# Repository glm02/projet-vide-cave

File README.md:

# Projet vide-cave — GEII

> **En bref** — Projet de BUT GEII : une carte électronique qui surveille et commande
> la pompe d'un vide-cave — **mesure du courant** du moteur, autotest périodique,
> affichage sur écran LCD, alertes par LED et buzzer. Conçue sous **KiCad**,
> programmée en **C sur PIC** (MPLAB X, MCC), étudiée sous **LTspice**, mise en scène
> dans **Blender**, suivie dans **Obsidian**.

| Bloc | Rôle |
|---|---|
| PIC16F1788 | Acquisition, décision, affichage et commande |
| Capteur de courant (ACS756) | Mesure du courant du moteur de la pompe |
| Optotriac + triac de puissance | Commande de la pompe sur le secteur, isolée de l'électronique basse tension |
| LCD 162B, LED, buzzer | Affichage de l'état et alertes |

Statut : conception en cours — voir plus bas ce qui reste à câbler et à valider.

**Ce que j'ai fait :** reprise et nettoyage de la carte KiCad, comparaison schéma/PCB/
nomenclature, dimensionnement de l'optotriac (MOC3041) avec bancs LTspice, maquette
3D de l'installation, visualisation interactive de la carte, et organisation du projet
pour travailler à deux sous Git.

---

Étude d'une commande de pompe vide-cave avec surveillance du courant, affichage et alarmes. Le projet KiCad de travail est la carte **G206_CAMEL_TP_CAO**, adaptée d'une ancienne carte. **Statut : EN COURS — non prêt pour fabrication.** L'étude de commande et de puissance reste à terminer : la présence des sources dans ce dépôt ne constitue pas une validation pour fabrication ou mise sous tension.
http://geii.pages.univ-lyon1.fr/cao/
## Ouvrir le projet

- **KiCad de travail (carte V2, Jules) :** [G206_CAMEL_TP_CAO.kicad_pro](03_Electronique/G206A_CAMEL_TP_CAO%20V2/G206_CAMEL_TP_CAO.kicad_pro).
- **Notes Obsidian :** ouvrir le dossier du projet comme coffre, puis [00 — Accueil](05_Notes/Obsidian/00%20-%20Accueil.md). Suivi des tâches : `05_Notes/Kanban vide-cave.base`.
- **Analyse de la carte et comparaison aux documents :** [rapport du 12 octobre 2026](05_Notes/Analyse_G206_2026-10-12/RAPPORT_ANALYSE.md).
- **Étude MOC3041 :** [dimensionnement proposé et bancs LTspice](05_Notes/Etude_MOC3041/DIMENSIONNEMENT.md), [simulation Anatomy](07_Visualisation_Anatomy/simulation.html) et [travail à deux sur GitHub](05_Notes/Archives/09%20-%20Travail%20a%20deux%20et%20MOC3041.md). Les valeurs secteur restent conditionnées au triac et à la pompe réels.
- **Firmware principal :** ouvrir `08_Firmware/Projet_vide_cave_1.X` dans MPLAB X (PIC16F1788, MCC Classic, XC8). Le programme est dans `main.c` ; les versions précédentes sont dans `anciennes_versions/`. Les essais du TP sont dans `08_Firmware/SAE22`.
- **Composants :** [CSV détaillé, une ligne par référence](03_Electronique/G206A_CAMEL_TP_CAO%20V2/Composants_G206.csv) et [nomenclature groupée](03_Electronique/G206A_CAMEL_TP_CAO%20V2/Nomenclature_G206_groupee.csv). Le schéma compte 24 composants ; le CSV détaillé indique aussi les écarts avec le PCB.
- **Rapport de pré-étude :** [document Word](01_Documents/Rapport/Rapport_pre-etude_vide-cave.docx).
- **Synoptique modifiable :** [Synoptique V3](02_Synoptiques/Synoptique%20V3.drawio).
- **Maquette :** [fichier Blender](04_Maquette_3D/Vide_cave_GEII.blend) et [notice](04_Maquette_3D/LISEZ_MOI.md).
- **Visualisation pédagogique Anatomy :** ouvrir [index.html](07_Visualisation_Anatomy/index.html) dans un navigateur, ou consulter [l'aperçu](07_Visualisation_Anatomy/preview.png) et [la notice](07_Visualisation_Anatomy/README.md). Cette visualisation explique le projet ; elle ne produit pas le PCB. Sur GitHub, télécharger ou cloner le dépôt pour ouvrir la page localement.

## Sources et versions

| Dossier | Contenu et statut |
| --- | --- |
| `01_Documents` | Consignes, rapport Word, présentation et planning |
| `02_Synoptiques` | Sources Draw.io et versions exportées |
| `03_Electronique/G206A_CAMEL_TP_CAO V2` | **Carte de travail V2** avec l'optotriac (Jules), schéma, PCB et bibliothèques locales |
| `03_Electronique/Carte_vide_cave_PIC_Allegro_TRIAC` | Proposition indépendante ; ne remplace pas la carte G206 et n'applique pas son routage simple face |
| `03_Electronique/Projets_KiCad_initiaux` | Versions antérieures conservées comme références |
| `04_Maquette_3D` | Scène Blender, rendus et scripts existants |
| `05_Notes/Obsidian` | Notes à jour : code, mesures, 6N136, soutenance |
| `05_Notes/Kanban` | Une note par tâche, affichées par `Kanban vide-cave.base` |
| `05_Notes/Archives` | Anciennes notes (G206 v1, ancien code) |
| `05_Notes/Analyse_G206_2026-10-12` | Rapport de contrôle et tableau de comparaison des composants |
| `06_Archives_et_exports` | Archives, anciens exports, projets MPLAB abandonnés (`Firmware_abandonne`) et journal de rangement |
| `07_Visualisation_Anatomy` | Visualisation du fonctionnement et des blocs du projet |
| `08_Firmware` | Projets MPLAB X : `Projet_vide_cave_1.X` (programme du vide-cave) et `SAE22` (essais du TP) |

Les Gerbers et typons déjà présents sont des exports antérieurs. **Les régénérer seulement après validation du schéma et du PCB** ; leur présence ne garantit pas leur concordance avec les sources actuelles.

## Consignes de conception

1. Router les connexions courantes sur **B.Cu, bleu**.
2. Limiter **F.Cu, rouge** à quelques straps filaires ; cette carte n'est pas à généraliser en double face.
3. Les composants supprimés du schéma lors de l'adaptation de l'ancienne carte sont à nettoyer sur le PCB.
4. Conserver les composants présents au schéma. Ne pas déplacer ni remplacer les autres composants conservés pour effectuer ce nettoyage.
5. Garder les règles KiCad existantes. La consigne bleu/straps est une décision de fabrication à vérifier visuellement, pas une restriction automatique du DRC.

Voir [les règles PCB](05_Notes/Archives/02%20-%20Regles%20PCB.md) et [les problèmes à résoudre](05_Notes/Archives/04%20-%20Anomalies%20et%20verifications.md). Les valeurs de courant et la plaque moteur restent à renseigner ; les hypothèses inscrites dans une variante ne sont pas des mesures de la pompe.

## Travailler depuis un autre ordinateur

Installer Git, KiCad **10.0.6 ou une version 10 compatible**, puis Obsidian si souhaité. Les bibliothèques locales de G206 sont dans le dépôt et leurs tables utilisent `${KIPRJMOD}` : conserver l'ensemble du dossier KiCad au même endroit. Ne pas ajouter de bibliothèques par des chemins absolus propres à un PC.

```sh
git clone https://github.com/glm02/projet-vide-cave.git
cd projet-vide-cave
git pull --ff-only
```

Ouvrir ensuite le `.kicad_pro` indiqué plus haut. Pour enregistrer et partager une session :

```sh
git status
git add -- "03_Electronique/G206A_CAMEL_TP_CAO V2" "05_Notes"
git diff --cached --stat
git commit -m "Décrire la modification réalisée sur la carte"
git push
```

Adapter les chemins ajoutés aux documents réellement modifiés. Pour un rapport Word, une présentation ou une scène Blender, fermer le fichier avant de le versionner. Faire `git pull --ff-only` avant de commencer une nouvelle session. **Une personne à la fois sur le même schéma/PCB ou document binaire** : Git conserve l'historique mais ne fusionne pas automatiquement un routage ou un Word. Si le pull refuse, conserver les changements locaux et résoudre l'écart avant de poursuivre ; ne pas forcer le push.

Le schéma peut être modifié volontairement sans importer immédiatement toutes les différences dans le PCB. Avant « Mettre à jour le PCB depuis le schéma », vérifier les composants, empreintes, réseaux et conséquences dans le rapport : les divergences de R3, R4 et R7 nécessitent une décision explicite.

## Sauvegardes et portabilité

Git versionne les sources, bibliothèques et documents utiles. Il ignore les préférences KiCad `.kicad_prl`, les verrous, caches, sauvegardes automatiques, copies temporaires de l'analyse, état des fenêtres Obsidian et les dossiers de compilation MPLAB (`build`, `dist`…). Les fichiers ignorés restent sur le PC : le dépôt distant ne les sauvegarde pas. Les archives documentaires existantes sont conservées.

Les scripts historiques de la variante et quelques anciennes notices utilisent encore des chemins propres au PC d'origine. Ils sont conservés comme sources historiques ; leur exécution sur un autre poste peut demander une adaptation des chemins d'outils. Le [guide Git du coffre](05_Notes/Archives/07%20-%20Guide%20Git%20et%20portabilite.md) distingue ces scripts de l'ouverture du projet G206.

Le dépôt contient des documents scolaires, bibliothèques locales et ressources tierces. Aucun changement de licence globale n'est imposé aux fichiers préexistants. Les ressources Anatomy conservent leur licence et leur attribution propres.

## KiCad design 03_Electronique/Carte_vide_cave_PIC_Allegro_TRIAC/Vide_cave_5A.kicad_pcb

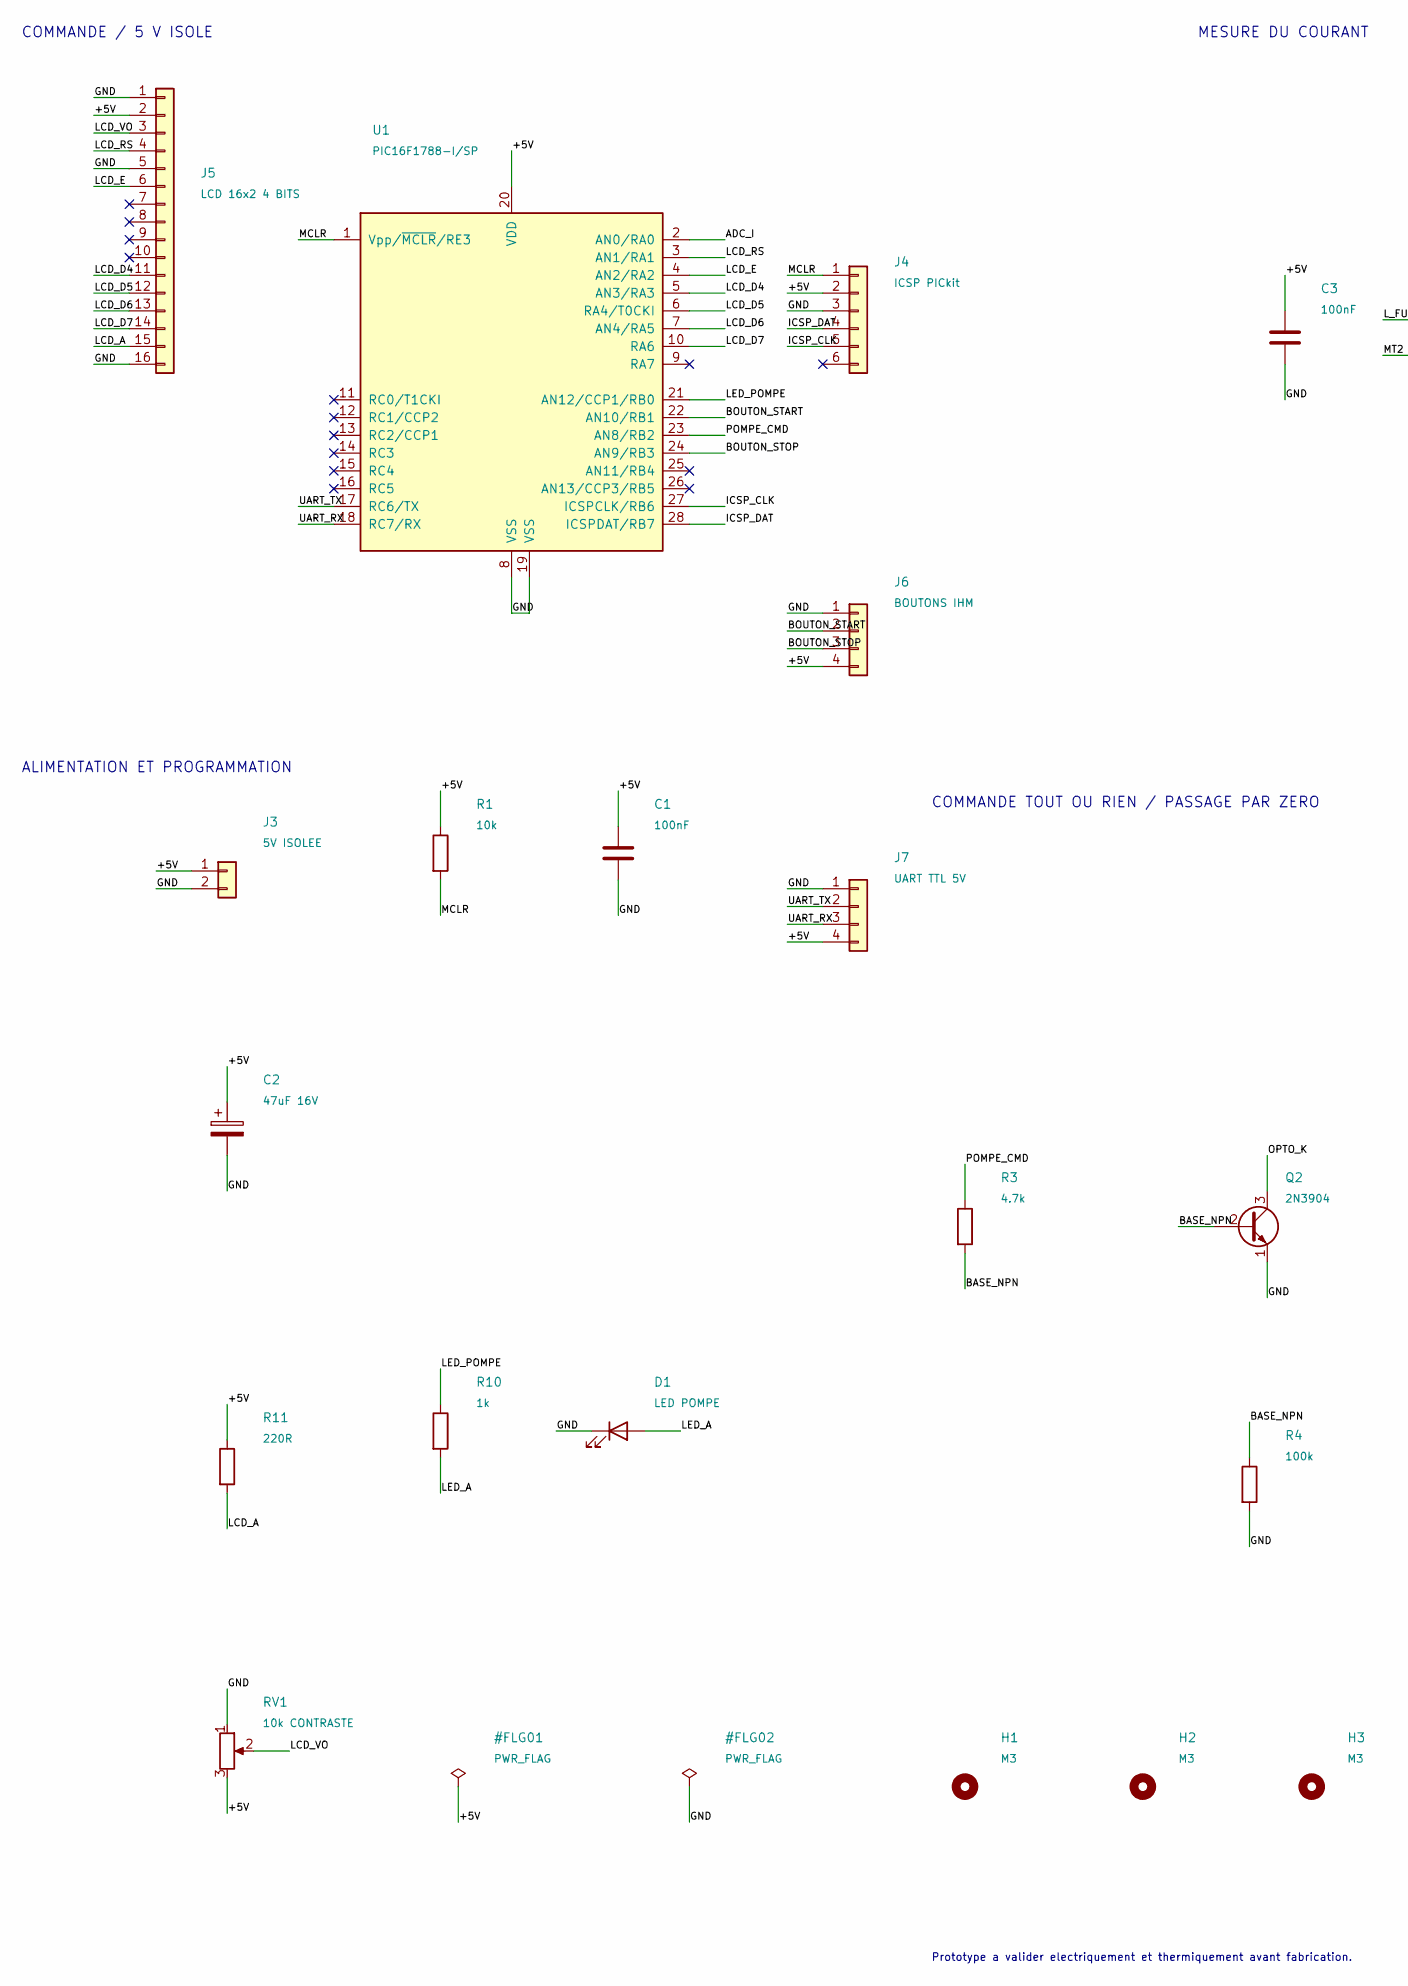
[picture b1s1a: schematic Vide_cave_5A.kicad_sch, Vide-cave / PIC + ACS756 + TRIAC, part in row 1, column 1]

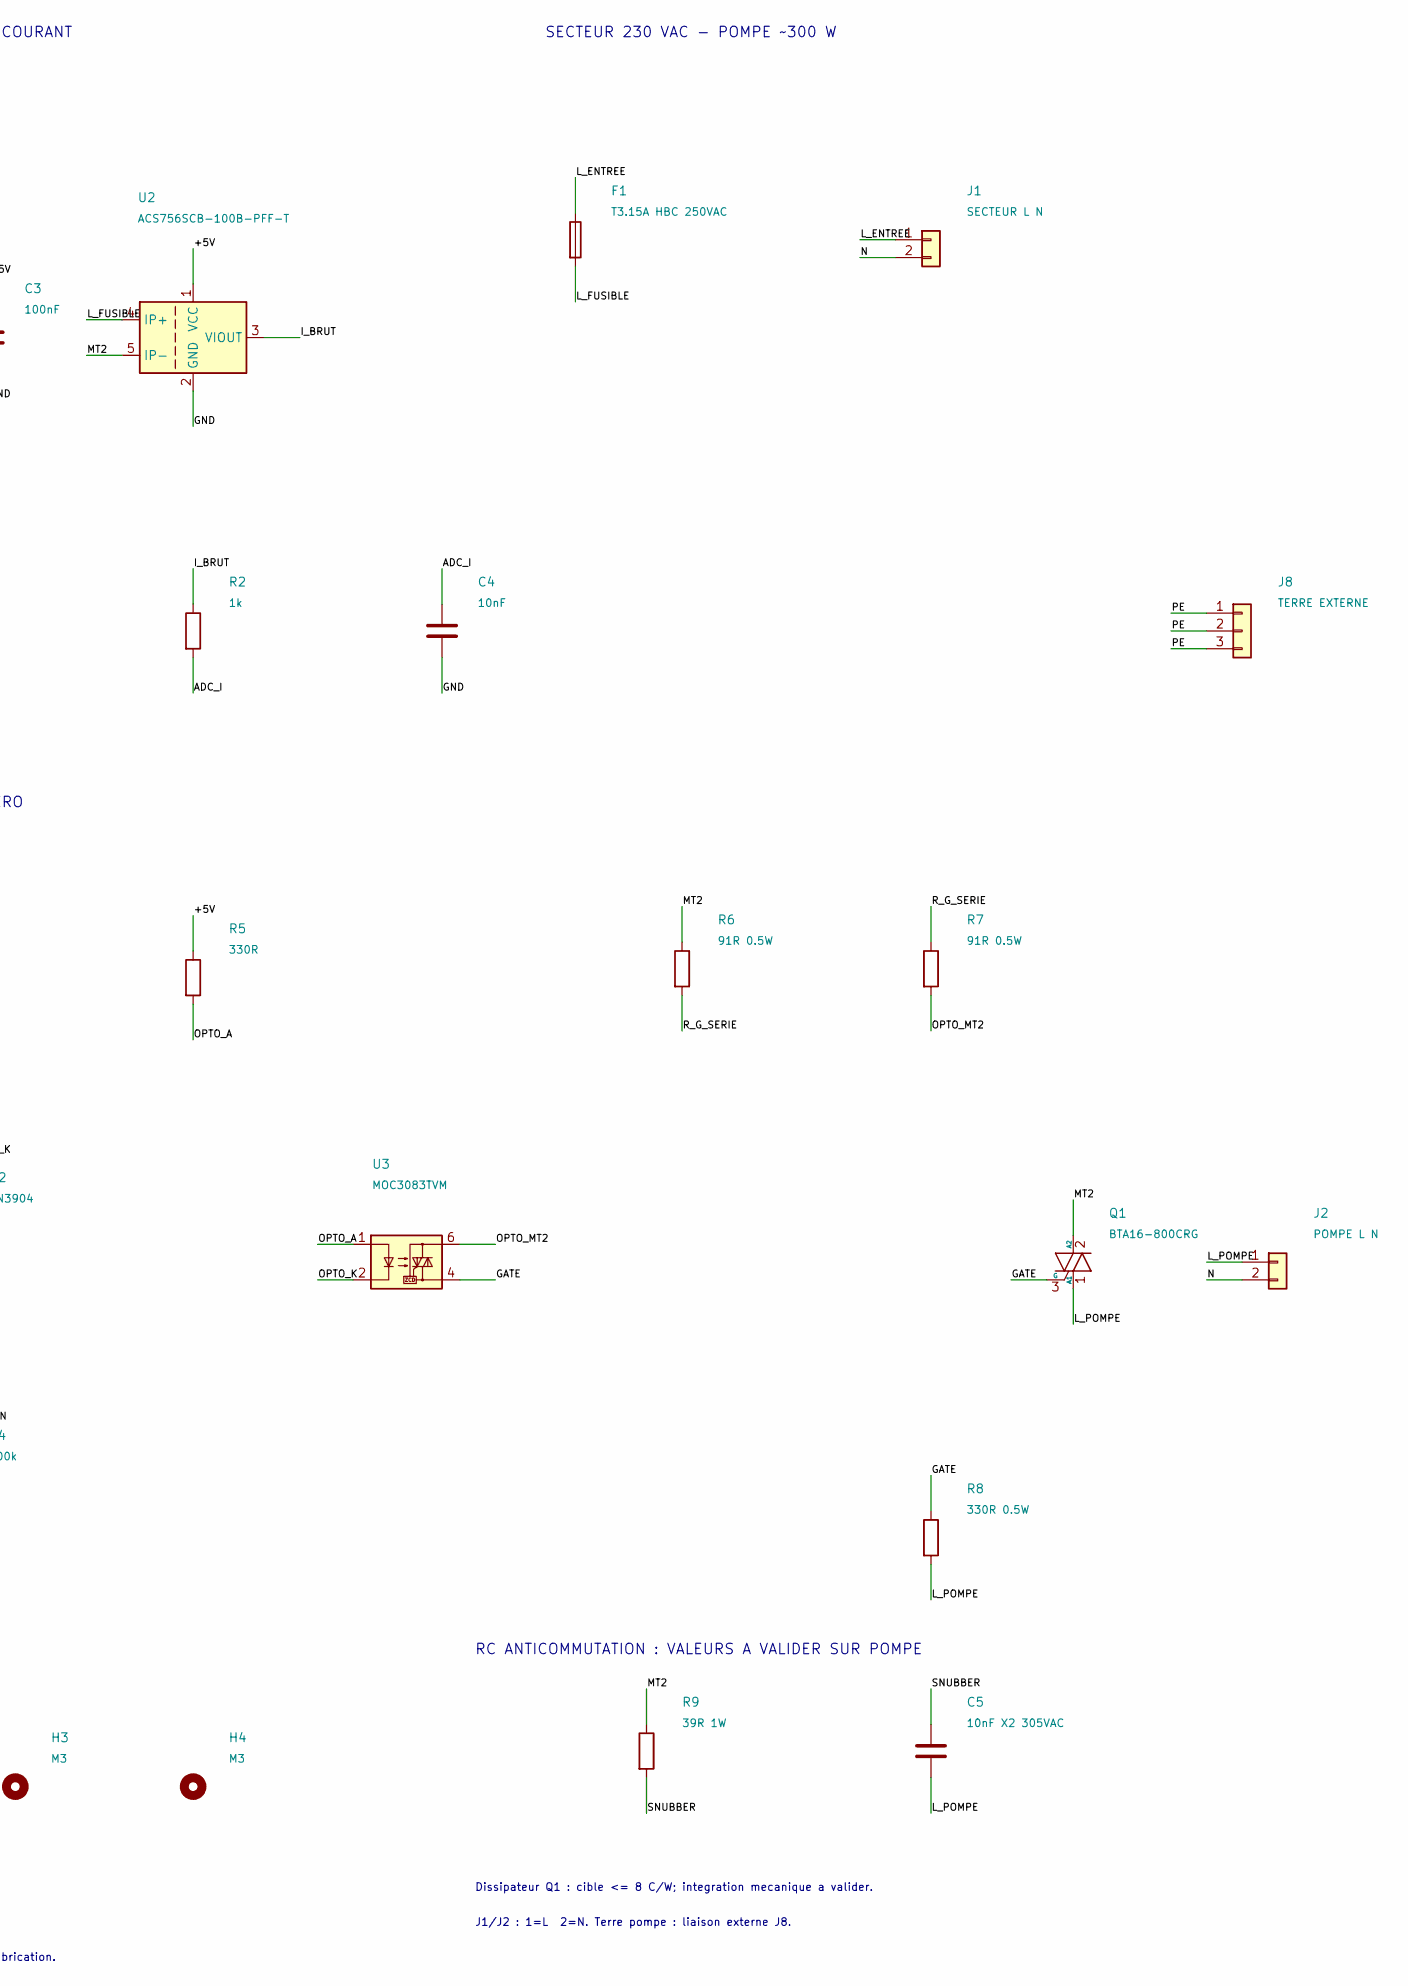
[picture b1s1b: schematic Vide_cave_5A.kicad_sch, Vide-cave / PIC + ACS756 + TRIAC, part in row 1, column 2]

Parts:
C1, C3: 100nF; C_Disc_D5.0mm_W2.5mm_P2.50mm
C2: 47uF 16V; CP_Radial_D6.3mm_P2.50mm
C4: 10nF; C_Disc_D5.0mm_W2.5mm_P2.50mm
C5: 10nF X2 305VAC; C_Rect_L19.0mm_W5.0mm_P15.00mm_MKS4
D1: LED POMPE; LED_D3.0mm
F1: T3.15A HBC 250VAC; Fuseholder_Littelfuse_445_030_series_5x20mm
H1, H2, H3, H4: M3; MountingHole_3.2mm_M3
J1: SECTEUR L N; RND_205_00298_P10_drill1_4
J2: POMPE L N; RND_205_00298_P10_drill1_4
J3: 5V ISOLEE; TerminalBlock_Phoenix_MKDS-1,5-2_1x02_P5.00mm_Horizontal
J4: ICSP PICkit; PinHeader_1x06_P2.54mm_Vertical
J5: LCD 16x2 4 BITS; PinHeader_1x16_P2.54mm_Vertical
J6: BOUTONS IHM; PinHeader_1x04_P2.54mm_Vertical
J7: UART TTL 5V; PinHeader_1x04_P2.54mm_Vertical
J8: TERRE EXTERNE
Q1: BTA16-800CRG; TO-220-3_Vertical
Q2: 2N3904; TO-92_Inline_Wide
R1: 10k; R_Axial_DIN0207_L6.3mm_D2.5mm_P7.62mm_Horizontal
R2, R10: 1k; R_Axial_DIN0207_L6.3mm_D2.5mm_P7.62mm_Horizontal
R3: 4.7k; R_Axial_DIN0207_L6.3mm_D2.5mm_P7.62mm_Horizontal
R4: 100k; R_Axial_DIN0207_L6.3mm_D2.5mm_P7.62mm_Horizontal
R5: 330R; R_Axial_DIN0207_L6.3mm_D2.5mm_P7.62mm_Horizontal
R6, R7: 91R 0.5W; R_Axial_DIN0207_L6.3mm_D2.5mm_P10.16mm_Horizontal
R8: 330R 0.5W; R_Axial_DIN0207_L6.3mm_D2.5mm_P10.16mm_Horizontal
R9: 39R 1W; R_Axial_DIN0411_L9.9mm_D3.6mm_P15.24mm_Horizontal
R11: 220R; R_Axial_DIN0207_L6.3mm_D2.5mm_P7.62mm_Horizontal
RV1: 10k CONTRASTE; Potentiometer_Bourns_3296W_Vertical
U1: PIC16F1788-I/SP; DIP-28_W7.62mm_LongPads
U2: ACS756SCB-100B-PFF-T; ACS756_PFF
U3: MOC3083TVM; MOC3083TVM_slot

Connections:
/+5V: C1.1, C2.1, C3.1, J3.1, J4.2, J5.2, J6.4, J7.4, R1.1, R5.1, R11.1, RV1.3, U1.20 (VDD), U2.1 (VCC)
/ADC_I: C4.1, R2.2, U1.2 (AN0/RA0)
/BASE_NPN: Q2.2 (B), R3.2, R4.1
/BOUTON_START: J6.2, U1.22 (AN10/RB1)
/BOUTON_STOP: J6.3, U1.24 (AN9/RB3)
/GATE: Q1.3 (G), R8.1, U3.4
/GND: C1.2, C2.2, C3.2, C4.2, D1.1 (K), J3.2, J4.3, J5.1, J5.5, J5.16, J6.1, J7.1, Q2.1 (E), R4.2, RV1.1, U1.8 (VSS), U1.19 (VSS), U2.2 (GND)
/ICSP_CLK: J4.5, U1.27 (ICSPCLK/RB6)
/ICSP_DAT: J4.4, U1.28 (ICSPDAT/RB7)
/I_BRUT: R2.1, U2.3 (VIOUT)
/LCD_A: J5.15, R11.2
/LCD_D4: J5.11, U1.5 (AN3/RA3)
/LCD_D5: J5.12, U1.6 (RA4/T0CKI)
/LCD_D6: J5.13, U1.7 (AN4/RA5)
/LCD_D7: J5.14, U1.10 (RA6)
/LCD_E: J5.6, U1.4 (AN2/RA2)
/LCD_RS: J5.4, U1.3 (AN1/RA1)
/LCD_VO: J5.3, RV1.2
/LED_A: D1.2 (A), R10.2
/LED_POMPE: R10.1, U1.21 (AN12/CCP1/RB0)
/L_ENTREE: F1.1, J1.1
/L_FUSIBLE: F1.2, U2.4 (IP+)
/L_POMPE: C5.2, J2.1, Q1.1 (A1), R8.2
/MCLR: J4.1, R1.2, U1.1 (Vpp/~MCLR/RE3)
/MT2: Q1.2 (A2), R6.1, R9.1, U2.5 (IP-)
/N: J1.2, J2.2
/OPTO_A: R5.2, U3.1
/OPTO_K: Q2.3 (C), U3.2
/OPTO_MT2: R7.2, U3.6
/POMPE_CMD: R3.1, U1.23 (AN8/RB2)
/R_G_SERIE: R6.2, R7.1
/SNUBBER: C5.1, R9.2
/UART_RX: J7.3, U1.18 (RC7/RX)
/UART_TX: J7.2, U1.17 (RC6/TX)
unnamed: J8.1, J8.2, J8.3

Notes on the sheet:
COMMANDE / 5 V ISOLE
MESURE DU COURANT
SECTEUR 230 VAC - POMPE ~300 W
ALIMENTATION ET PROGRAMMATION
COMMANDE TOUT OU RIEN / PASSAGE PAR ZERO
RC ANTICOMMUTATION : VALEURS A VALIDER SUR POMPE
J1/J2 : 1=L 2=N. Terre pompe : liaison externe J8.
Dissipateur Q1 : cible <= 8 C/W; integration mecanique a valider.
Prototype a valider electriquement et thermiquement avant fabrication.

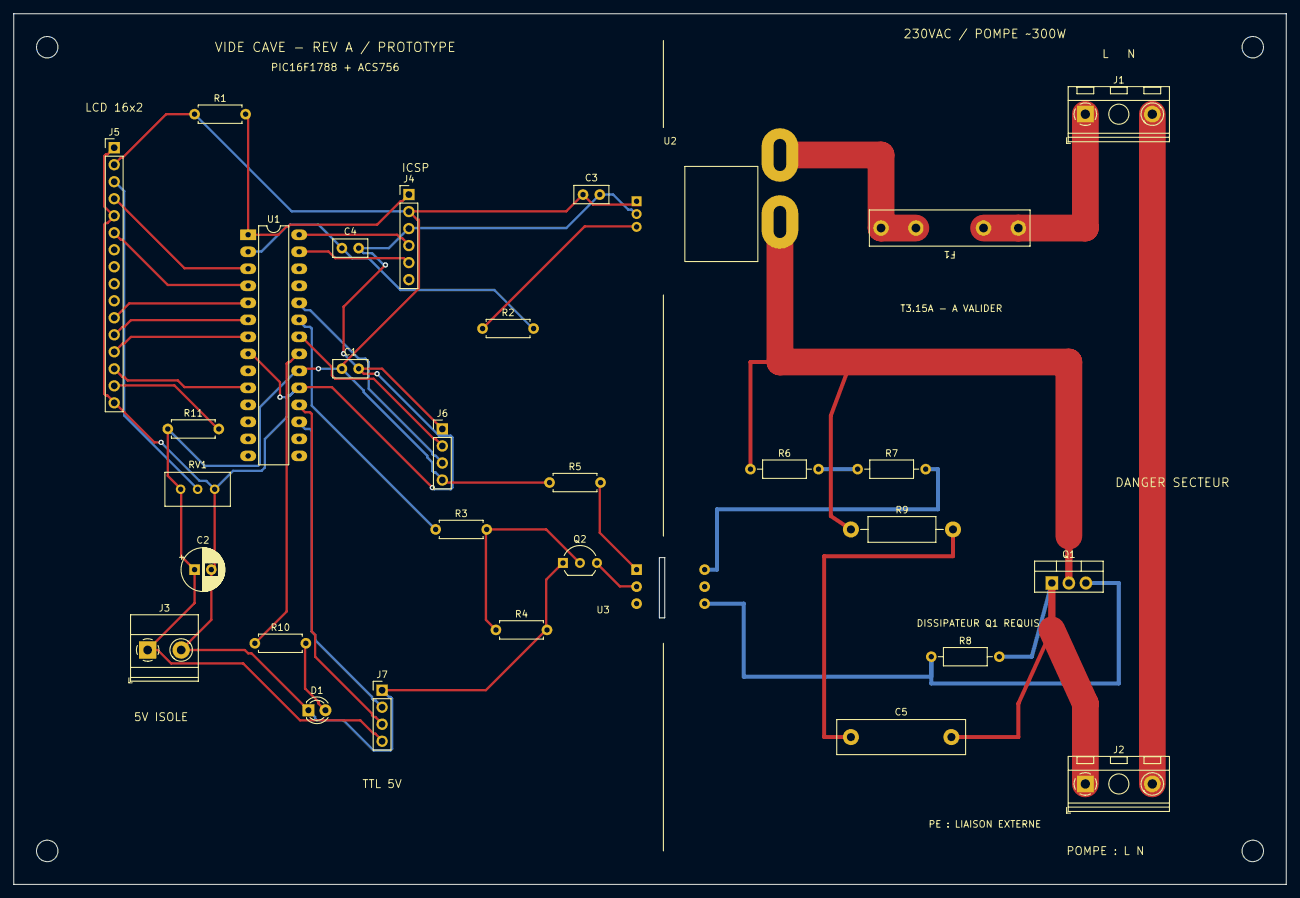
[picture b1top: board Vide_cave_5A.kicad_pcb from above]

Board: 2 copper layers, 190.0 x 130.0 mm, 35 parts (0 on the bottom side), 34 nets.

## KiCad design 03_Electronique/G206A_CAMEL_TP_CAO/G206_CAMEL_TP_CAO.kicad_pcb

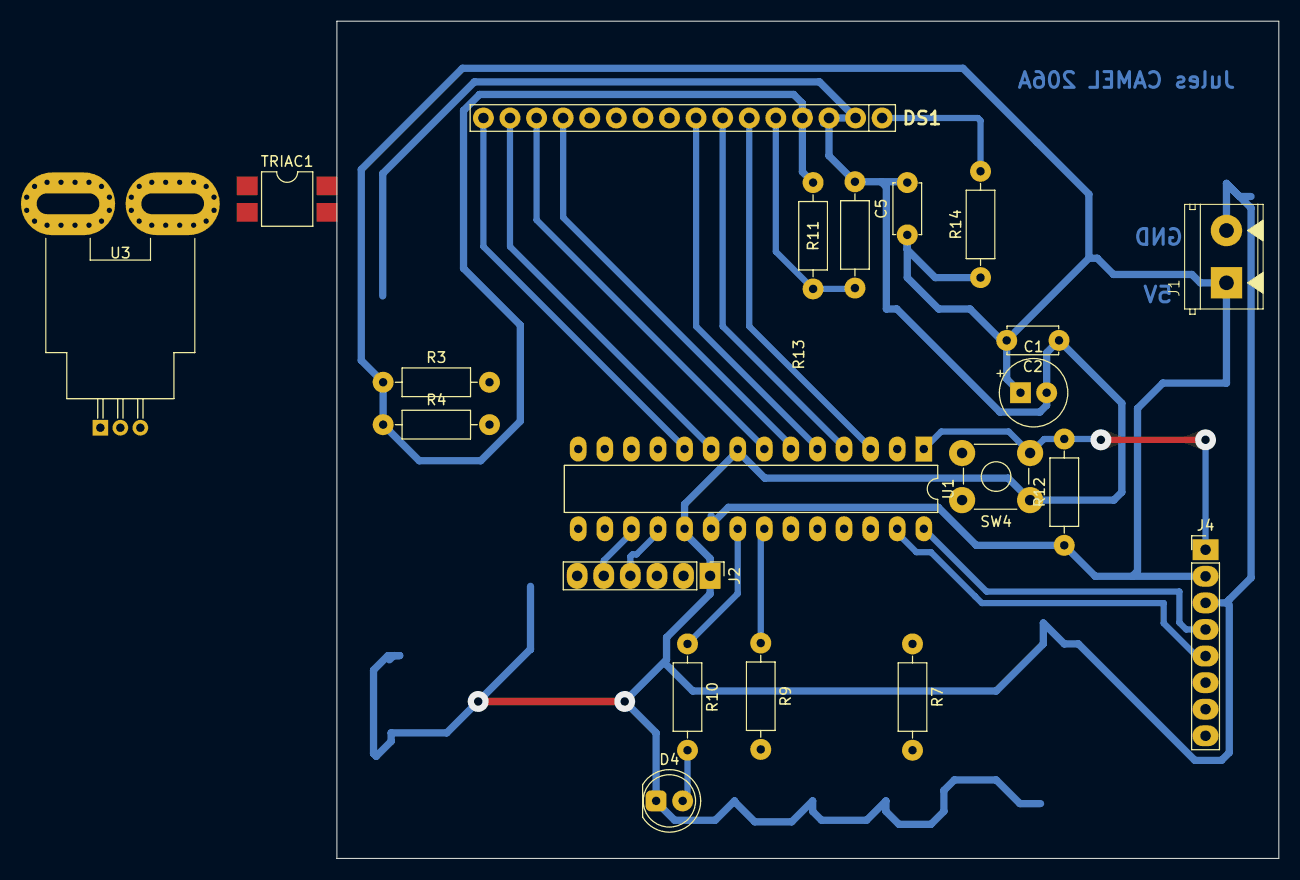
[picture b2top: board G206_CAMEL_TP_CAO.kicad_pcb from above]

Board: 2 copper layers, 90.0 x 80.0 mm, 21 parts (0 on the bottom side), 19 nets.

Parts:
C1: 47uF; CP_Radial_D6.3mm_P2.50mm
C2, C5: 100n; C_Disc_D4.7mm_W2.5mm_P5.00mm
D4: LED R; LED_D5.0mm
DS1: 162B-CC_BC-3LP; 162B
J1: Alimentation; Bornier_1x02_L10mm_W7.5mm_P5mm
J2: Série (TTL); PinHeader_1x06_P2.54mm_Vertical
J4: Conn_PIC_ICSP_ICD; PicKit_4_Snap_1x08_P2.54mm_Vertical
R3, R4, R12: 10k; R_Axial_DIN0207_L6.3mm_D2.5mm_P10.16mm_Horizontal
R7, R9, R10, R14: 270; R_Axial_DIN0207_L6.3mm_D2.5mm_P10.16mm_Horizontal
R11: 56k; R_Axial_DIN0207_L6.3mm_D2.5mm_P10.16mm_Horizontal
R13: 1,5k; R_Axial_DIN0207_L6.3mm_D2.5mm_P10.16mm_Horizontal
SW4: B3F-1000; SW_TH_Tactile_Omron_B3F-10xx
TRIAC1: octo-triac; SMDIP-4_W7.62mm
U1: PIC16F1788-xSP; DIP-28_W7.62mm_LongPads
U3: Capteur de courant; Allegro_CB_PFF

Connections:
+5V: C1.1, C2.2, C5.1, DS1.4 (VDD), J1.1, J4.2 (VDD), R3.1, R4.1, R11.1, R12.1, R14.1, U1.20 (VDD), U3.1 (VCC)
GND: C1.2, C2.1, C5.2, D4.1 (K), DS1.2 (LEDK), DS1.3 (VSS), J1.2, J2.1, J4.3 (VSS), R13.2, SW4.1, TRIAC1.2, U1.8 (VSS), U1.19 (VSS), U3.2 (GND)
ICSPCLK: J4.5 (PGC/ICSPCLK), U1.27 (ICSPCLK/RB6)
ICSPDAT: J4.4 (PGD/ICSPDAT), U1.28 (ICSPDAT/RB7)
LCD_D4: DS1.13 (DB4), U1.6 (RA4/T0CKI)
LCD_D5: DS1.14 (DB5), U1.7 (AN4/RA5)
LCD_D6: DS1.15 (DB6), U1.9 (RA7)
LCD_D7: DS1.16 (DB7), U1.10 (RA6)
LCD_E: DS1.8 (E), U1.5 (AN3/RA3)
LCD_RS: DS1.6 (RS), U1.3 (AN1/RA1)
LCD_RW: DS1.7 (R/~W), U1.4 (AN2/RA2)
unnamed: D4.2 (A), R10.2
unnamed: DS1.1 (LEDA), R14.2
unnamed: DS1.5 (Vo), R11.2, R13.1
unnamed: R9.1, U1.22 (AN10/RB1)
unnamed: R10.1, U1.21 (AN12/CCP1/RB0)
uC_RXD_TTL: J2.4, U1.18 (RC7/RX)
uC_TXD_TTL: J2.5, U1.17 (RC6/TX)
~MCLR: J4.1 (~MCLR/VPP), R12.2, SW4.2, U1.1 (Vpp/~MCLR/RE3)

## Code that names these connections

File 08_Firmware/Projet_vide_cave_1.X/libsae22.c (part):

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#pragma config FOSC = INTOSC    // Oscillator Selection->INTOSC oscillator: I/O function on CLKIN pin
#pragma config WDTE = OFF    // Watchdog Timer Enable->WDT disabled
#pragma config PWRTE = OFF    // Power-up Timer Enable->PWRT disabled
#pragma config MCLRE = ON    // MCLR Pin Function Select->MCLR/VPP pin function is MCLR
#pragma config CP = OFF    // Flash Program Memory Code Protection->Program memory code protection is disabled
#pragma config CPD = OFF    // Data Memory Code Protection->Data memory code protection is disabled
#pragma config BOREN = ON    // Brown-out Reset Enable->Brown-out Reset enabled
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// get/set LCD_RS aliases
#define LCD_RS_TRIS                 TRISAbits.TRISA1
#define LCD_RS_LAT                  LATAbits.LATA1
#define LCD_RS_PORT                 PORTAbits.RA1
#define LCD_RS_SetHigh()            do { LATAbits.LATA1 = 1; } while(0)
#define LCD_RS_SetLow()             do { LATAbits.LATA1 = 0; } while(0)
#define LCD_RS_Toggle()             do { LATAbits.LATA1 = ~LATAbits.LATA1; } while(0)
#define LCD_RS_GetValue()           PORTAbits.RA1

// get/set LCD_RW aliases
#define LCD_RW_TRIS                 TRISAbits.TRISA2
#define LCD_RW_LAT                  LATAbits.LATA2
#define LCD_RW_PORT                 PORTAbits.RA2
#define LCD_RW_SetHigh()            do { LATAbits.LATA2 = 1; } while(0)
#define LCD_RW_SetLow()             do { LATAbits.LATA2 = 0; } while(0)
#define LCD_RW_Toggle()             do { LATAbits.LATA2 = ~LATAbits.LATA2; } while(0)
#define LCD_RW_GetValue()           PORTAbits.RA2

// get/set LCD_E aliases
#define LCD_E_TRIS                 TRISAbits.TRISA3
#define LCD_E_LAT                  LATAbits.LATA3
#define LCD_E_PORT                 PORTAbits.RA3
#define LCD_E_SetHigh()            do { LATAbits.LATA3 = 1; } while(0)
#define LCD_E_SetLow()             do { LATAbits.LATA3 = 0; } while(0)
#define LCD_E_Toggle()             do { LATAbits.LATA3 = ~LATAbits.LATA3; } while(0)
#define LCD_E_GetValue()           PORTAbits.RA3

// get/set LCD_D4 aliases
#define LCD_D4_TRIS                 TRISAbits.TRISA4
#define LCD_D4_LAT                  LATAbits.LATA4
#define LCD_D4_PORT                 PORTAbits.RA4
#define LCD_D4_SetHigh()            do { LATAbits.LATA4 = 1; } while(0)
#define LCD_D4_SetLow()             do { LATAbits.LATA4 = 0; } while(0)
#define LCD_D4_Toggle()             do { LATAbits.LATA4 = ~LATAbits.LATA4; } while(0)
#define LCD_D4_GetValue()           PORTAbits.RA4

// get/set LCD_D5 aliases
#define LCD_D5_TRIS                 TRISAbits.TRISA5
#define LCD_D5_LAT                  LATAbits.LATA5
#define LCD_D5_PORT                 PORTAbits.RA5
#define LCD_D5_SetHigh()            do { LATAbits.LATA5 = 1; } while(0)
#define LCD_D5_SetLow()             do { LATAbits.LATA5 = 0; } while(0)
#define LCD_D5_Toggle()             do { LATAbits.LATA5 = ~LATAbits.LATA5; } while(0)
#define LCD_D5_GetValue()           PORTAbits.RA5

// get/set LCD_D7 aliases
#define LCD_D7_TRIS                 TRISAbits.TRISA6
#define LCD_D7_LAT                  LATAbits.LATA6
#define LCD_D7_PORT                 PORTAbits.RA6
#define LCD_D7_SetHigh()            do { LATAbits.LATA6 = 1; } while(0)
#define LCD_D7_SetLow()             do { LATAbits.LATA6 = 0; } while(0)
#define LCD_D7_Toggle()             do { LATAbits.LATA6 = ~LATAbits.LATA6; } while(0)
#define LCD_D7_GetValue()           PORTAbits.RA6

// get/set LCD_D6 aliases
#define LCD_D6_TRIS                 TRISAbits.TRISA7
#define LCD_D6_LAT                  LATAbits.LATA7
#define LCD_D6_PORT                 PORTAbits.RA7
#define LCD_D6_SetHigh()            do { LATAbits.LATA7 = 1; } while(0)
#define LCD_D6_SetLow()             do { LATAbits.LATA7 = 0; } while(0)
#define LCD_D6_Toggle()             do { LATAbits.LATA7 = ~LATAbits.LATA7; } while(0)
#define LCD_D6_GetValue()           PORTAbits.RA7

/**
 * 
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}

void LCD_Initialize(void) {
    //GPIO Init - RA7...RA1 digital outputs
    ANSELA &= 0x01;
    TRISA &= 0x01;
    
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
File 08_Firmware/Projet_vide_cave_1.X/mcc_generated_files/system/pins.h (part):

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// get/set IO_RA0 aliases
#define Capteur_COURANT_TRIS                 TRISAbits.TRISA0
#define Capteur_COURANT_LAT                  LATAbits.LATA0
#define Capteur_COURANT_PORT                 PORTAbits.RA0
#define Capteur_COURANT_WPU                  WPUAbits.WPUA0
#define Capteur_COURANT_OD                   ODCONAbits.
#define Capteur_COURANT_ANS                  ANSELAbits.ANSA0
#define Capteur_COURANT_SetHigh()            do { LATAbits.LATA0 = 1; } while(0)
#define Capteur_COURANT_SetLow()             do { LATAbits.LATA0 = 0; } while(0)
#define Capteur_COURANT_Toggle()             do { LATAbits.LATA0 = ~LATAbits.LATA0; } while(0)
#define Capteur_COURANT_GetValue()           PORTAbits.RA0
#define Capteur_COURANT_SetDigitalInput()    do { TRISAbits.TRISA0 = 1; } while(0)
#define Capteur_COURANT_SetDigitalOutput()   do { TRISAbits.TRISA0 = 0; } while(0)
#define Capteur_COURANT_SetPullup()          do { WPUAbits.WPUA0 = 1; } while(0)
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// get/set IO_RB0 aliases
#define LED_TRIS                 TRISBbits.TRISB0
#define LED_LAT                  LATBbits.LATB0
#define LED_PORT                 PORTBbits.RB0
#define LED_WPU                  WPUBbits.WPUB0
#define LED_OD                   ODCONBbits.
#define LED_ANS                  ANSELBbits.ANSB0
#define LED_SetHigh()            do { LATBbits.LATB0 = 1; } while(0)
#define LED_SetLow()             do { LATBbits.LATB0 = 0; } while(0)
#define LED_Toggle()             do { LATBbits.LATB0 = ~LATBbits.LATB0; } while(0)
#define LED_GetValue()           PORTBbits.RB0
#define LED_SetDigitalInput()    do { TRISBbits.TRISB0 = 1; } while(0)
#define LED_SetDigitalOutput()   do { TRISBbits.TRISB0 = 0; } while(0)
#define LED_SetPullup()          do { WPUBbits.WPUB0 = 1; } while(0)
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// get/set IO_RB1 aliases
#define BUZZER_TRIS                 TRISBbits.TRISB1
#define BUZZER_LAT                  LATBbits.LATB1
#define BUZZER_PORT                 PORTBbits.RB1
#define BUZZER_WPU                  WPUBbits.WPUB1
#define BUZZER_OD                   ODCONBbits.
#define BUZZER_ANS                  ANSELBbits.ANSB1
#define BUZZER_SetHigh()            do { LATBbits.LATB1 = 1; } while(0)
#define BUZZER_SetLow()             do { LATBbits.LATB1 = 0; } while(0)
#define BUZZER_Toggle()             do { LATBbits.LATB1 = ~LATBbits.LATB1; } while(0)
#define BUZZER_GetValue()           PORTBbits.RB1
#define BUZZER_SetDigitalInput()    do { TRISBbits.TRISB1 = 1; } while(0)
#define BUZZER_SetDigitalOutput()   do { TRISBbits.TRISB1 = 0; } while(0)
#define BUZZER_SetPullup()          do { WPUBbits.WPUB1 = 1; } while(0)
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// get/set IO_RB2 aliases
#define OPTO_TRIAC_TRIS                 TRISBbits.TRISB2
#define OPTO_TRIAC_LAT                  LATBbits.LATB2
#define OPTO_TRIAC_PORT                 PORTBbits.RB2
#define OPTO_TRIAC_WPU                  WPUBbits.WPUB2
#define OPTO_TRIAC_OD                   ODCONBbits.
#define OPTO_TRIAC_ANS                  ANSELBbits.ANSB2
#define OPTO_TRIAC_SetHigh()            do { LATBbits.LATB2 = 1; } while(0)
#define OPTO_TRIAC_SetLow()             do { LATBbits.LATB2 = 0; } while(0)
#define OPTO_TRIAC_Toggle()             do { LATBbits.LATB2 = ~LATBbits.LATB2; } while(0)
#define OPTO_TRIAC_GetValue()           PORTBbits.RB2
#define OPTO_TRIAC_SetDigitalInput()    do { TRISBbits.TRISB2 = 1; } while(0)
#define OPTO_TRIAC_SetDigitalOutput()   do { TRISBbits.TRISB2 = 0; } while(0)
#define OPTO_TRIAC_SetPullup()          do { WPUBbits.WPUB2 = 1; } while(0)
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// get/set IO_RB3 aliases
#define LED_D1_TRIS                 TRISBbits.TRISB3
#define LED_D1_LAT                  LATBbits.LATB3
#define LED_D1_PORT                 PORTBbits.RB3
#define LED_D1_WPU                  WPUBbits.WPUB3
#define LED_D1_OD                   ODCONBbits.
#define LED_D1_ANS                  ANSELBbits.ANSB3
#define LED_D1_SetHigh()            do { LATBbits.LATB3 = 1; } while(0)
#define LED_D1_SetLow()             do { LATBbits.LATB3 = 0; } while(0)
#define LED_D1_Toggle()             do { LATBbits.LATB3 = ~LATBbits.LATB3; } while(0)
#define LED_D1_GetValue()           PORTBbits.RB3
#define LED_D1_SetDigitalInput()    do { TRISBbits.TRISB3 = 1; } while(0)
#define LED_D1_SetDigitalOutput()   do { TRISBbits.TRISB3 = 0; } while(0)
#define LED_D1_SetPullup()          do { WPUBbits.WPUB3 = 1; } while(0)
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// get/set IO_RC6 aliases
#define IO_RC6_TRIS                 TRISCbits.TRISC6
#define IO_RC6_LAT                  LATCbits.LATC6
#define IO_RC6_PORT                 PORTCbits.RC6
#define IO_RC6_WPU                  WPUCbits.WPUC6
#define IO_RC6_OD                   ODCONCbits.
#define IO_RC6_ANS                  ANSELCbits.ANSC6
#define IO_RC6_SetHigh()            do { LATCbits.LATC6 = 1; } while(0)
#define IO_RC6_SetLow()             do { LATCbits.LATC6 = 0; } while(0)
#define IO_RC6_Toggle()             do { LATCbits.LATC6 = ~LATCbits.LATC6; } while(0)
#define IO_RC6_GetValue()           PORTCbits.RC6
#define IO_RC6_SetDigitalInput()    do { TRISCbits.TRISC6 = 1; } while(0)
#define IO_RC6_SetDigitalOutput()   do { TRISCbits.TRISC6 = 0; } while(0)
#define IO_RC6_SetPullup()          do { WPUCbits.WPUC6 = 1; } while(0)
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// get/set IO_RC7 aliases
#define IO_RC7_TRIS                 TRISCbits.TRISC7
#define IO_RC7_LAT                  LATCbits.LATC7
#define IO_RC7_PORT                 PORTCbits.RC7
#define IO_RC7_WPU                  WPUCbits.WPUC7
#define IO_RC7_OD                   ODCONCbits.
#define IO_RC7_ANS                  ANSELCbits.ANSC7
#define IO_RC7_SetHigh()            do { LATCbits.LATC7 = 1; } while(0)
#define IO_RC7_SetLow()             do { LATCbits.LATC7 = 0; } while(0)
#define IO_RC7_Toggle()             do { LATCbits.LATC7 = ~LATCbits.LATC7; } while(0)
#define IO_RC7_GetValue()           PORTCbits.RC7
#define IO_RC7_SetDigitalInput()    do { TRISCbits.TRISC7 = 1; } while(0)
#define IO_RC7_SetDigitalOutput()   do { TRISCbits.TRISC7 = 0; } while(0)
#define IO_RC7_SetPullup()          do { WPUCbits.WPUC7 = 1; } while(0)
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

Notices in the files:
08_Firmware/Projet_vide_cave_1.X/mcc_generated_files/system/pins.h:
© [2026] Microchip Technology Inc. and its subsidiaries.
